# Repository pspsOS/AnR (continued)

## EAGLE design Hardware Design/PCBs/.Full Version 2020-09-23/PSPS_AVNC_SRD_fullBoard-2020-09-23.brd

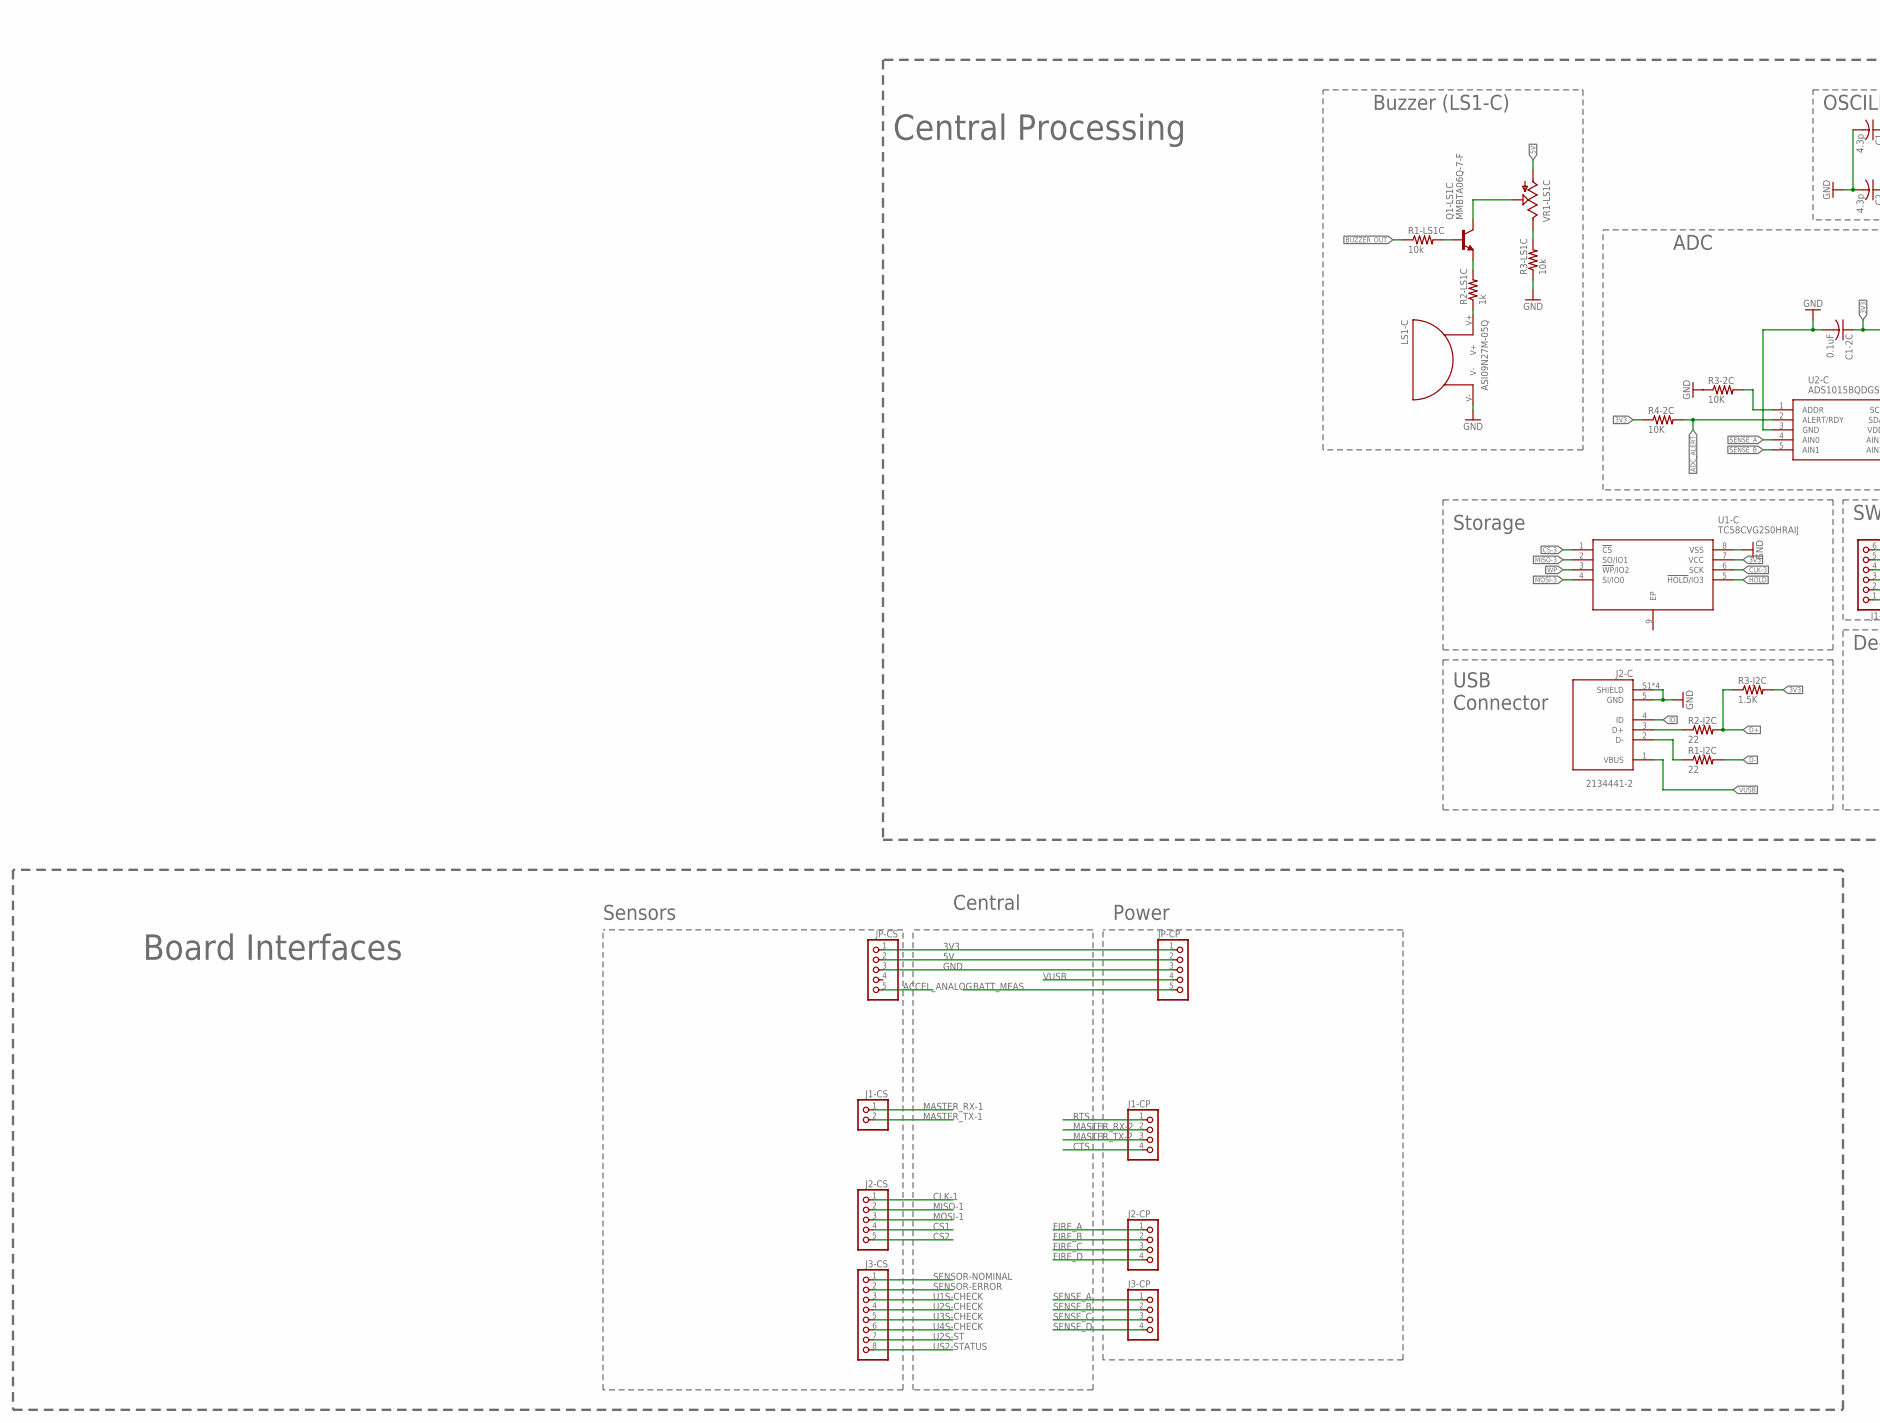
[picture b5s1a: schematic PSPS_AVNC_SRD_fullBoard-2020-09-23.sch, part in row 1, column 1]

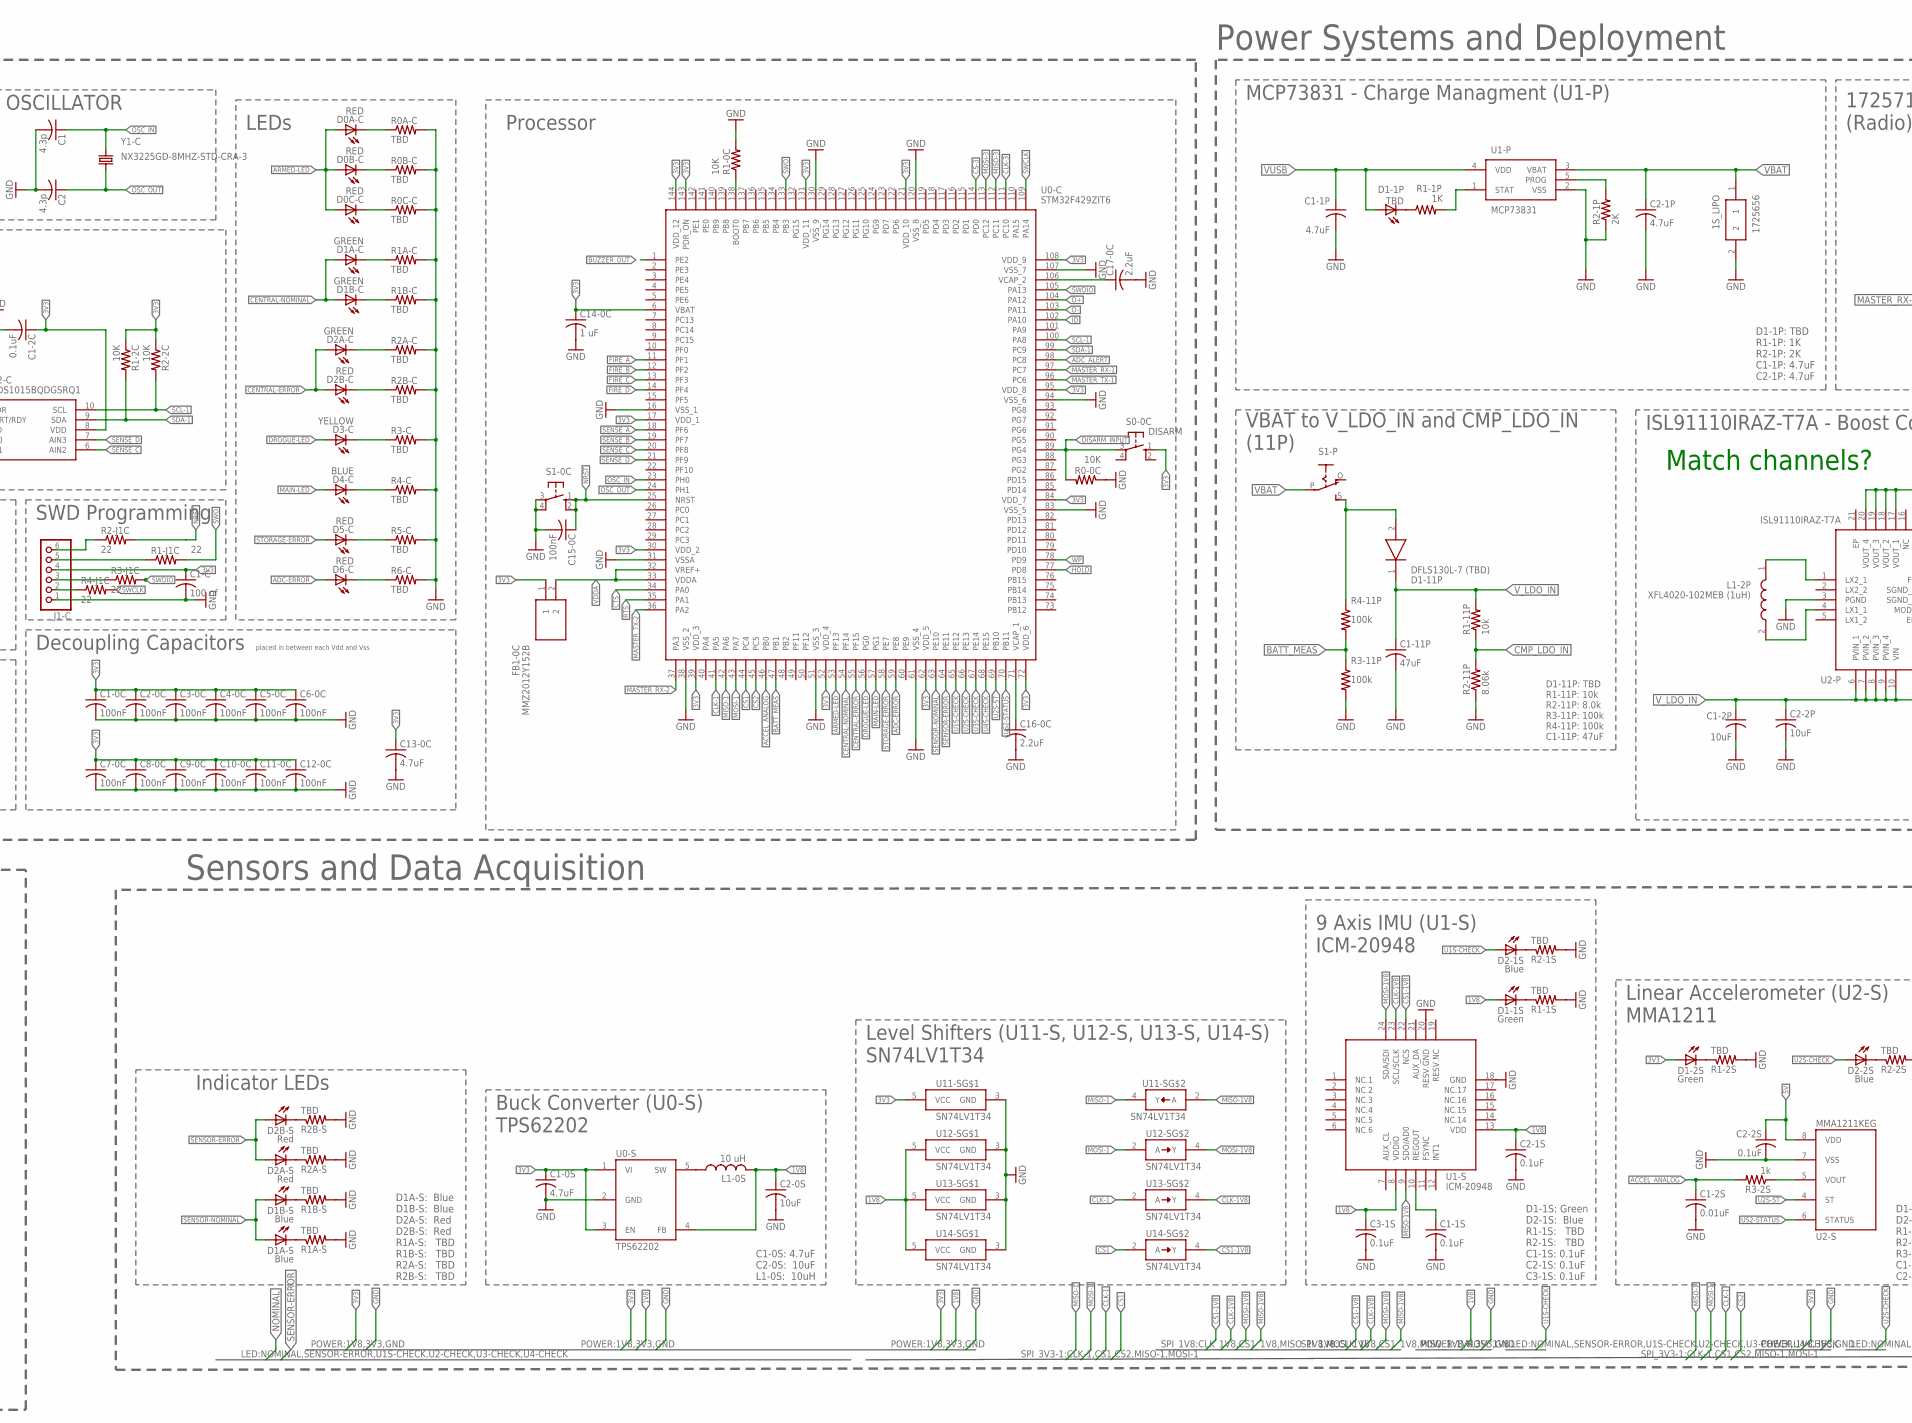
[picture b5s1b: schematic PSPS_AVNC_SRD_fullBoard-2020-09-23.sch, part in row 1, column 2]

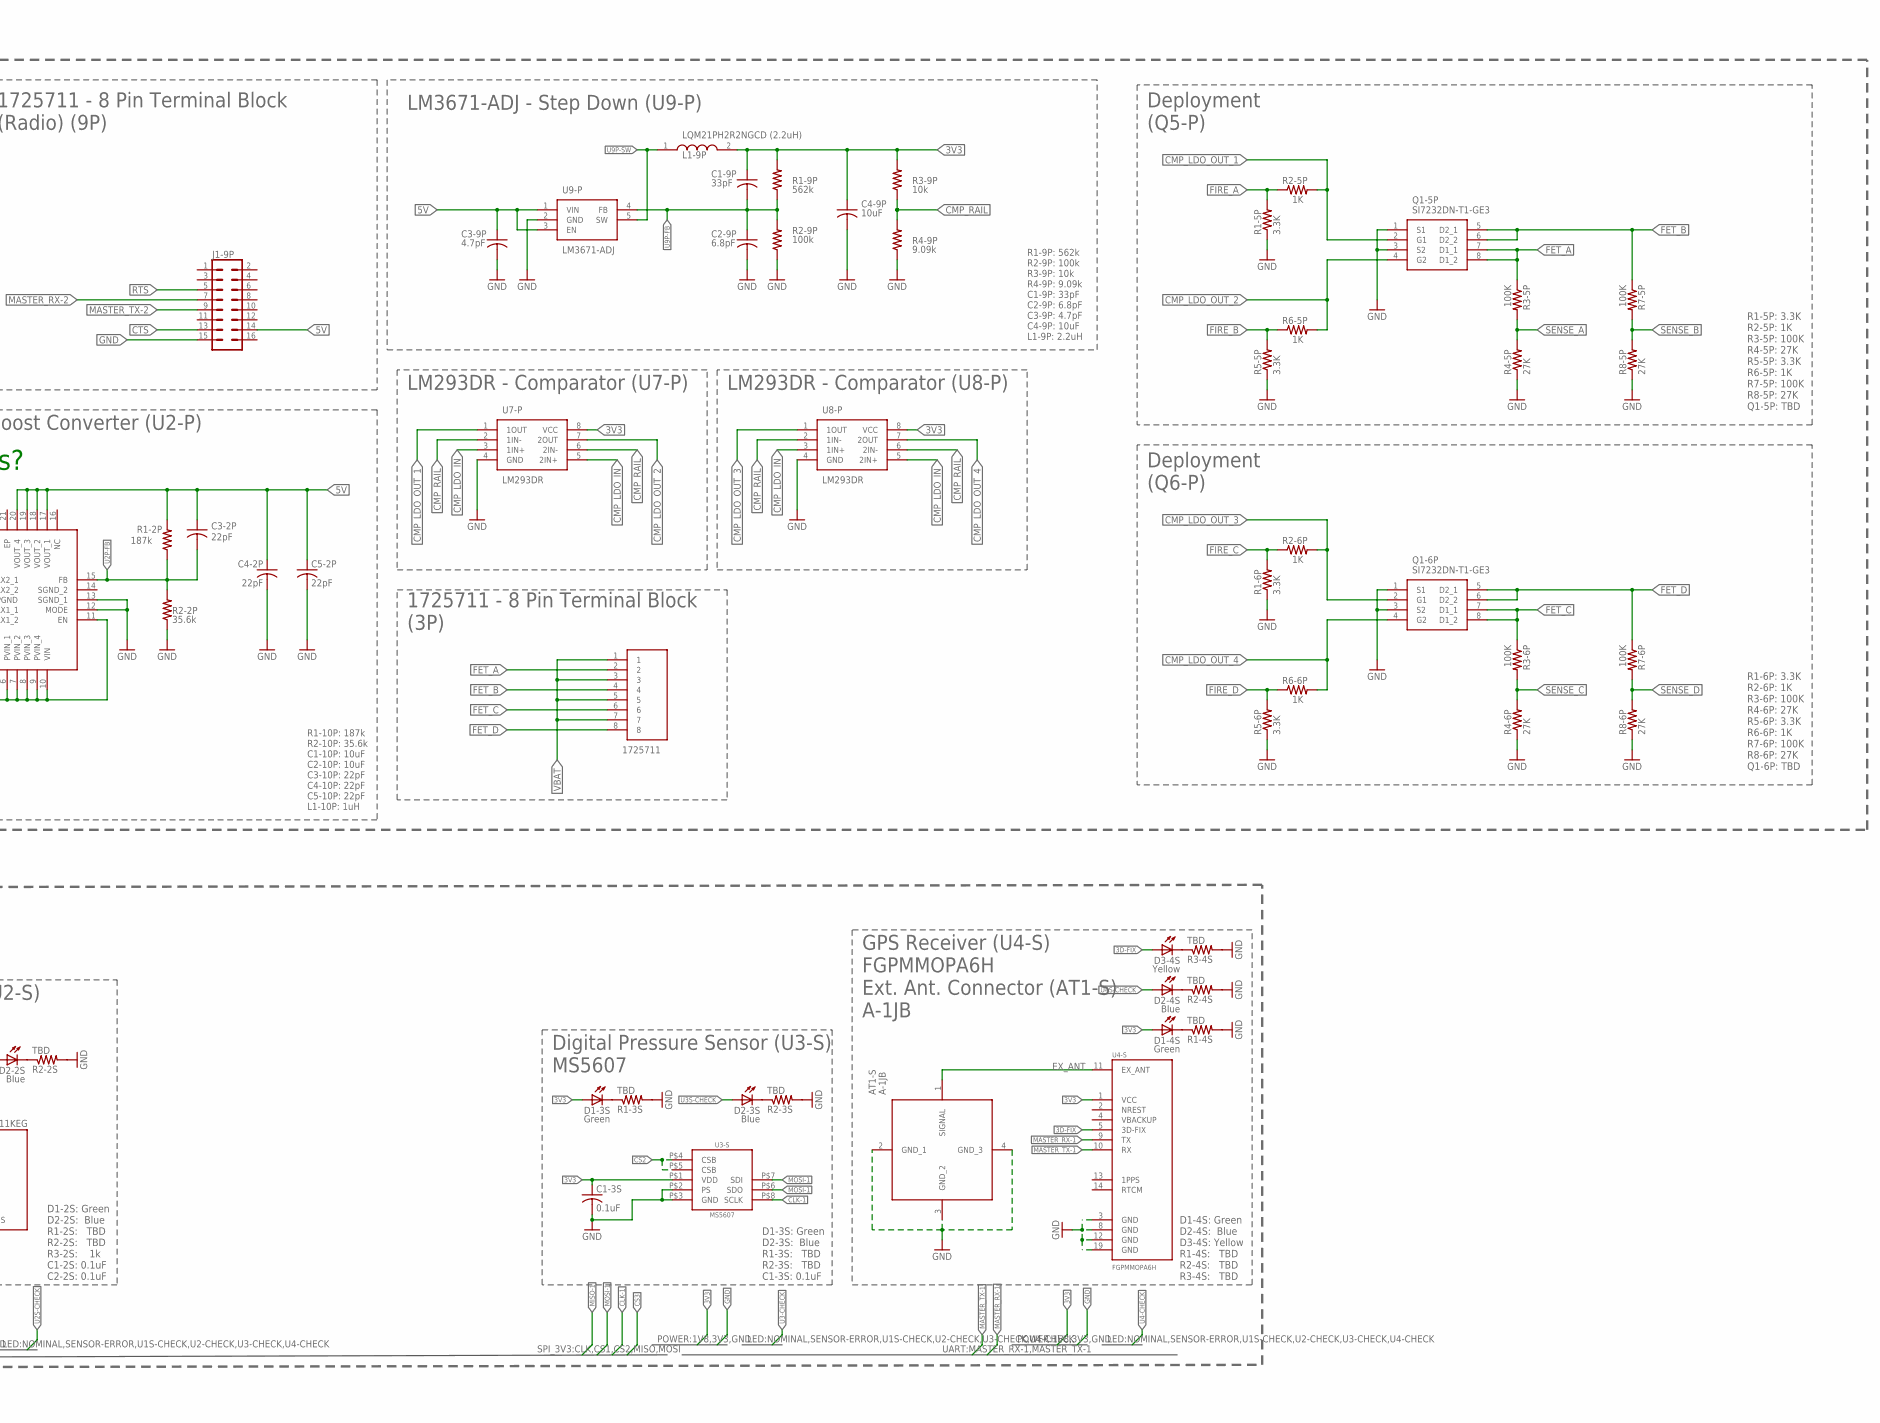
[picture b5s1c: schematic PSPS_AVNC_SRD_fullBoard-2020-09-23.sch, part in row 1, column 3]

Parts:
1S_LIPO: 1725656
AT1-S: A-1JB; A1JB
C1, C2: 4.3p; C0805
C1-0C, C2-0C, C3-0C, C4-0C, C5-0C, C6-0C, C7-0C, C8-0C, C9-0C, C10-0C, C11-0C, C12-0C, C15-0C: 100nF; C0805
C1-0S, C1-1P, C2-1P, C13-0C: 4.7uF; C0805
C1-1S, C1-2C, C1-3S, C2-1S, C2-2S, C3-1S: 0.1uF; C0805
C1-2P, C2-0S, C2-2P, C4-9P: 10uF; C0805
C1-2S: 0.01uF; C0805
C1-9P: 33pF; C0805
C1-11P: 47uF; C0805
C1-C: 100 nf; C0805
C2-9P: 6.8pF; C0805
C3-2P, C4-2P, C5-2P: 22pF; C0805
C3-9P: 4.7pF; C0805
C14-0C: 1 uF; C0805
C16-0C, C17-0C: 2.2uF; C0805
D0A-C, D0B-C, D0C-C, D2B-C, D5-C, D6-C: RED; CHIPLED_0805
D1-1P: TBD; CHIPLED_0805
D1-1S, D1-2S, D1-3S, D1-4S: Green; CHIPLED_0805
D1-11P: DFLS130L-7 (TBD); POWERDI_123
D1A-C, D1B-C, D2A-C: GREEN; CHIPLED_0805
D1A-S, D1B-S, D2-1S, D2-2S, D2-3S, D2-4S: Blue; CHIPLED_0805
D2A-S, D2B-S: Red; CHIPLED_0805
D3-4S: Yellow; CHIPLED_0805
D3-C: YELLOW; CHIPLED_0805
D4-C: BLUE; CHIPLED_0805
FB1-0C: MMZ2012Y152B; BEADC2012X105N
J1-9P: CONN_08X2; 2X8
J1-C: PINHD-1X6; 1X06
J1-CP, J2-CP, J3-CP: PINHD-1X4; 1X04
J1-CS: PINHD-1X2; 1X02
J2-C: 2134441-2; TE_2134441-2
J2-CS: PINHD-1X5; 1X05
J2-P: 1725711
J3-CS: PINHD-1X8; 1X08
JP-CP: PINHD-1X5; 1X05
JP-CS: PINHD-1X5; 1X05
L1-0S: 10 uH; PF0560NL
L1-2P: XFL4020-102MEB (1uH); XFL4020
L1-9P: LQM21PH2R2NGCD (2.2uH); INDC2012X100N
LS1-C: ASI09N27M-05Q
Q1-5P, Q1-6P: SI7232DN-T1-GE3; POWERPAK-1212-8
Q1-LS1C: MMBTA06Q-7-F; SOT23
R0-0C, R1-0C, R1-2C, R2-2C, R3-2C, R4-2C: 10K; R0805
R0A-C, R0B-C, R0C-C, R1A-C, R1B-C, R2A-C, R2B-C, R3-C, R4-C, R5-C, R6-C: TBD; M0805
R1-1P: 1K; R0805
R1-1S, R1-2S, R1-3S, R1-4S, R1A-S, R1B-S, R2-1S, R2-2S, R2-3S, R2-4S, R2A-S, R2B-S, R3-4S: TBD; R0805
R1-2P: 187k; R0805
R1-5P, R1-6P, R5-5P, R5-6P: 3.3K; M0805
R1-9P: 562k; R0805
R1-11P, R1-LS1C, R3-9P, R3-LS1C: 10k; R0805
R1-J1C, R1-J2C, R2-J1C, R2-J2C, R3-J1C, R4-J1C: 22; M0805
R2-1P: 2K; R0805
R2-2P: 35.6k; R0805
R2-5P, R2-6P, R6-5P, R6-6P: 1K; M0805
R2-9P, R3-11P, R4-11P: 100k; R0805
R2-11P: 8.06k; R0805
R2-LS1C, R3-2S: 1k; R0805
R3-5P, R3-6P, R7-5P, R7-6P: 100K; M0805
R3-J2C: 1.5K; M0805
R4-5P, R4-6P, R8-5P, R8-6P: 27K; M0805
R4-9P: 9.09k; R0805
S0-0C: DISARM; B3F-10XX
S1-0C: 10-XX; B3F-10XX
S1-P: EG1218S; EG1218
U0-C: STM32F429ZIT6; QFP50P2200X2200X160-144N
U0-S: TPS62202; SOT95P280X145-5
U1-C: TC58CVG2S0HRAIJ; SON127P800X600X80-9N
U1-P: MCP73831; SOT95P270X145-5N
U1-S: ICM-20948; QFN40P300X300X105-25T159X175
U2-C: ADS1015BQDGSRQ1; SOP50P490X110-10N
U2-P: ISL91110IRAZ-T7A; QFN50P400X400X100-21N
U2-S: MMA1211KEG; SOIC127P1041X355-16N
U3-S: MS5607
U4-S: FGPMMOPA6H; SOIC127P1800X470-20N
U7-P, U8-P: LM293DR; SOIC127P600X175-8N
U9-P: LM3671-ADJ; SOT95P280X145-5N
U11-S, U12-S, U13-S, U14-S: SN74LV1T34; SOT65P210X110-5
VR1-LS1C: TRIM_US-LI10; LI10
Y1-C: NX3225GD-8MHZ-STD-CRA-3; 3.2X2.5_KX-7

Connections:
1V8: C2-0S.1, C2-1S.1, C3-1S.1, D1-1S.A, L1-0S.P$2 (2), U0-S.4 (FB), U1-S.8 (VDDIO), U1-S.13 (VDD), U12-S.5 (VCC), U13-S.5 (VCC), U14-S.5 (VCC)
3D-FIX: D3-4S.A, U4-S.5 (3D-FIX)
3V3: C1-0C.1, C1-0S.1, C1-2C.1, C1-3S.1, C1-9P.1, C1-C.1, C2-0C.1, C3-0C.1, C4-0C.1, C4-9P.1, C5-0C.1, C6-0C.1, C7-0C.1, C8-0C.1, C9-0C.1, C10-0C.1, C11-0C.1, C12-0C.1, C13-0C.1, C14-0C.1, D1-2S.A, D1-3S.A, D1-4S.A, FB1-0C.1, J1-C.4, JP-CP.1, JP-CS.1, L1-9P.2, R1-2C.1, R1-9P.2, R2-2C.1, R3-9P.2, R3-J2C.2, R4-2C.1, S0-0C.1 (S), U0-C.6 (VBAT), U0-C.17 (VDD_1), U0-C.30 (VDD_2), U0-C.39 (VDD_3), U0-C.52 (VDD_4), U0-C.62 (VDD_5), U0-C.72 (VDD_6), U0-C.84 (VDD_7), U0-C.95 (VDD_8), U0-C.108 (VDD_9), U0-C.121 (VDD_10), U0-C.131 (VDD_11), U0-C.143 (PDR_ON), U0-C.144 (VDD_12), U0-S.1 (VI), U0-S.3 (EN), U1-C.7 (VCC), U2-C.8 (VDD), U3-S.P$1 (VDD), U4-S.1 (VCC), U7-P.8 (VCC), U8-P.8 (VCC), U11-S.5 (VCC)
5V: C2-2S.1, C3-2P.1, C3-9P.1, C4-2P.1, C5-2P.1, J1-9P.14, JP-CP.2, JP-CS.2, R1-2P.2, U2-P.17 (VOUT_1), U2-P.18 (VOUT_2), U2-P.19 (VOUT_3), U2-P.20 (VOUT_4), U2-S.8 (VDD), U9-P.1 (VIN), U9-P.3 (EN), VR1-LS1C.A
ACCEL_ANALOG: C1-2S.1, JP-CS.5, R3-2S.2, U0-C.46 (PB0)
ADC-ERROR: D6-C.A, U0-C.59 (PE8)
ADC_ALERT: R4-2C.2, U0-C.98 (PC8), U2-C.2 (ALERT/RDY)
ADDR: R3-2C.2, U2-C.1 (ADDR)
ARMED-LED: D0A-C.A, D0B-C.A, D0C-C.A, U0-C.53 (PF13)
BATT_MEAS: JP-CP.5, R3-11P.1, R4-11P.2, U0-C.47 (PB1)
BOOT0: R1-0C.1, U0-C.138 (BOOT0)
BUZZER_OUT: R1-LS1C.1, U0-C.1 (PE2)
CENTRAL-ERROR: D2A-C.A, D2B-C.A, U0-C.55 (PF15)
CENTRAL-NOMINAL: D1A-C.A, D1B-C.A, U0-C.54 (PF14)
CLK-1: J2-CS.1, U0-C.41 (PA5), U3-S.P$8 (SCLK), U13-S.2 (A)
CLK-1V8: U1-S.23 (SCL/SCLK), U13-S.4 (Y)
CLK-3: U0-C.111 (PC10), U1-C.6 (SCK)
CMP_LDO_IN: R1-11P.1, R2-11P.2, U7-P.3 (1IN+), U7-P.5 (2IN+), U8-P.3 (1IN+), U8-P.5 (2IN+)
CMP_LDO_OUT_1: Q1-5P.2 (G1), R2-5P.2, U7-P.1 (1OUT)
CMP_LDO_OUT_2: Q1-5P.4 (G2), R6-5P.2, U7-P.7 (2OUT)
CMP_LDO_OUT_3: Q1-6P.2 (G1), R2-6P.2, U8-P.1 (1OUT)
CMP_LDO_OUT_4: Q1-6P.4 (G2), R6-6P.2, U8-P.7 (2OUT)
CMP_RAIL: R3-9P.1, R4-9P.2, U7-P.2 (1IN-), U7-P.6 (2IN-), U8-P.2 (1IN-), U8-P.6 (2IN-)
CS1: J2-CS.4, U0-C.44 (PC4), U14-S.2 (A)
CS1-1V8: U1-S.22 (NCS), U14-S.4 (Y)
CS2: J2-CS.5, U0-C.45 (PC5), U3-S.P$4 (CSB), U3-S.P$5 (CSB)
CS-3: U0-C.114 (PD0), U1-C.1 (!CS)
CTS: J1-9P.13, J1-CP.4, U0-C.34 (PA0)
D0A-C_R0A-C: D0A-C.C, R0A-C.1
D0B-C_R0B-C: D0B-C.C, R0B-C.1
D0C-C_R0C-C: D0C-C.C, R0C-C.1
D1-1P_R1-1P: D1-1P.C, R1-1P.1
D1-1S_R1-1S: D1-1S.C, R1-1S.1
D1-2S_R1-2S: D1-2S.C, R1-2S.1
D1-3S_R1-3S: D1-3S.C, R1-3S.1
D1-4S_R1-4S: D1-4S.C, R1-4S.1
D1A-C_R1A-C: D1A-C.C, R1A-C.1
D1A-S_R1A-S: D1A-S.C, R1A-S.1
D1B-C_R1B-C: D1B-C.C, R1B-C.1
D1B-S_R1B-S: D1B-S.C, R1B-S.1
D2-1S_R2-1S: D2-1S.C, R2-1S.1
D2-2S_R2-2S: D2-2S.C, R2-2S.1
D2-3S_R2-3S: D2-3S.C, R2-3S.1
D2-4S_R2-4S: D2-4S.C, R2-4S.1
D2A-C_R2A-C: D2A-C.C, R2A-C.1
D2A-S_R2A-S: D2A-S.C, R2A-S.1
D2B-C_R2B-C: D2B-C.C, R2B-C.1
D2B-S_R2B-S: D2B-S.C, R2B-S.1
D3-4S_R3-4S: D3-4S.C, R3-4S.1
D3-C_R3-C: D3-C.C, R3-C.1
D4-C_R4-C: D4-C.C, R4-C.1
D5-C_R5-C: D5-C.C, R5-C.1
D6-C_R6-C: D6-C.C, R6-C.1
D+: R2-J2C.2, R3-J2C.1, U0-C.104 (PA12)
D+_R2-J1C: J2-C.3 (D+), R2-J2C.1
D-: R1-J2C.2, U0-C.103 (PA11)
D-_R1-J1C: J2-C.2 (D-), R1-J2C.1
DISARM_INPUT: R0-0C.2, S0-0C.3, U0-C.89 (PG4)
DROGUE-LED: D3-C.A, U0-C.56 (PG0)
EX_ANT: AT1-S.1 (SIGNAL), U4-S.11 (EX_ANT)
FET_A: J2-P.2, Q1-5P.7 (D1_1), Q1-5P.8 (D1_2), R3-5P.1
FET_B: J2-P.4, Q1-5P.5 (D2_1), Q1-5P.6 (D2_2), R7-5P.1
FET_C: J2-P.6, Q1-6P.7 (D1_1), Q1-6P.8 (D1_2), R3-6P.1
FET_D: J2-P.8, Q1-6P.5 (D2_1), Q1-6P.6 (D2_2), R7-6P.1
FIRE_A: J2-CP.1, R1-5P.2, R2-5P.1, U0-C.11 (PF1)
FIRE_B: J2-CP.2, R5-5P.2, R6-5P.1, U0-C.12 (PF2)
FIRE_C: J2-CP.3, R1-6P.2, R2-6P.1, U0-C.13 (PF3)
FIRE_D: J2-CP.4, R5-6P.2, R6-6P.1, U0-C.14 (PF4)
GND: 1S_LIPO.2, AT1-S.2 (GND_1), AT1-S.3 (GND_2), AT1-S.4 (GND_3), C1.2, C1-0C.2, C1-0S.2, C1-1P.2, C1-1S.2, C1-2C.2, C1-2P.2, C1-2S.2, C1-3S.2, C1-11P.2, C1-C.2, C2.2, C2-0C.2, C2-0S.2, C2-1P.2, C2-1S.2, C2-2P.2, C2-2S.2, C2-9P.2, C3-0C.2, C3-1S.2, C3-9P.2, C4-0C.2, C4-2P.2, C4-9P.2, C5-0C.2, C5-2P.2, C6-0C.2, C7-0C.2, C8-0C.2, C9-0C.2, C10-0C.2, C11-0C.2, C12-0C.2, C13-0C.2, C14-0C.2, C15-0C.2, C16-0C.2, C17-0C.2, J1-9P.15, J1-C.1, J2-C.5 (GND), J2-C.S1 (SHIELD), J2-C.S2 (SHIELD), J2-C.S3 (SHIELD), J2-C.S4 (SHIELD), JP-CP.3, JP-CS.3, LS1-C.V-, Q1-5P.1 (S1), Q1-5P.3 (S2), Q1-6P.1 (S1), Q1-6P.3 (S2), R0-0C.1, R0A-C.2, R0B-C.2, R0C-C.2, R1-0C.2, R1-1S.2, R1-2S.2, R1-3S.2, R1-4S.2, R1-5P.1, R1-6P.1, R1A-C.2, R1A-S.2, R1B-C.2, R1B-S.2, R2-1P.1, R2-1S.2, R2-2P.1, R2-2S.2, R2-3S.2, R2-4S.2, R2-9P.1, R2-11P.1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
HOLD: U0-C.77 (PD8), U1-C.5 (!HOLD!/IO3)
ID: J2-C.4 (ID), U0-C.102 (PA10)
J1-C_R1-J1C: J1-C.5, R1-J1C.1
J1-C_R2-J1C: J1-C.6, R2-J1C.1
MAIN-LED: D4-C.A, U0-C.57 (PG1)
MASTER_RX-1: J1-CS.1, U0-C.97 (PC7), U4-S.9 (TX)
MASTER_RX-2: J1-9P.7, J1-CP.2, U0-C.37 (PA3)
MASTER_TX-1: J1-CS.2, U0-C.96 (PC6), U4-S.10 (RX)
MASTER_TX-2: J1-9P.9, J1-CP.3, U0-C.36 (PA2)
MISO-1: J2-CS.2, U0-C.42 (PA6), U11-S.4 (Y)
MISO-1V8: U1-S.9 (SDO/AD0), U11-S.2 (A)
MISO-3: U0-C.112 (PC11), U1-C.2 (SO/IO1)
MOSI-1: J2-CS.3, U0-C.43 (PA7), U3-S.P$6 (SDO), U3-S.P$7 (SDI), U12-S.2 (A)
MOSI-1V8: U1-S.24 (SDA/SDI), U12-S.4 (Y)
MOSI-3: U0-C.113 (PC12), U1-C.4 (SI/IO0)
NRST: C15-0C.1, R2-J1C.2, S1-0C.1 (S), S1-0C.2 (S1), U0-C.25 (NRST)
OSC_IN: C1.1, U0-C.23 (PH0), Y1-C.3 (2)
OSC_OUT: C2.1, U0-C.24 (PH1), Y1-C.1
Q1-LS1C_R2-LS1C: Q1-LS1C.3 (E), R2-LS1C.2
R1-LS1C_Q1-LS1C: Q1-LS1C.1 (B), R1-LS1C.2
R2-LS1C_LS1-C: LS1-C.V+, R2-LS1C.1
REGOUT: C1-1S.1, U1-S.10 (REGOUT)
RTS: J1-9P.5, J1-CP.1, U0-C.35 (PA1)
SCL-1: R2-2C.2, U0-C.100 (PA8), U2-C.10 (SCL)
SDA-1: R1-2C.2, U0-C.99 (PC9), U2-C.9 (SDA)
SENSE_A: J3-CP.1, R3-5P.2, R4-5P.2, U0-C.18 (PF6), U2-C.4 (AIN0)
SENSE_B: J3-CP.2, R7-5P.2, R8-5P.2, U0-C.19 (PF7), U2-C.5 (AIN1)
SENSE_C: J3-CP.3, R3-6P.2, R4-6P.2, U0-C.20 (PF8), U2-C.6 (AIN2)
SENSE_D: J3-CP.4, R7-6P.2, R8-6P.2, U0-C.21 (PF9), U2-C.7 (AIN3)
SENSOR-ERROR: D2A-S.A, D2B-S.A, J3-CS.2, U0-C.64 (PE11)
SENSOR-NOMINAL: D1A-S.A, D1B-S.A, J3-CS.1, U0-C.63 (PE10)
STORAGE-ERROR: D5-C.A, U0-C.58 (PE7)
SWCLK: J1-C.2, R4-J1C.1, R4-J1C.2, U0-C.109 (PA14)
SWDIO: J1-C.3, R3-J1C.1, R3-J1C.2, U0-C.105 (PA13)
SWO: R1-J1C.2, U0-C.133 (PB3)
U0S-SW: L1-0S.P$1 (1), U0-S.5 (SW)
U1P-PROG: R2-1P.2, U1-P.5 (PROG)
U1P-STAT: R1-1P.2, U1-P.1 (STAT)
U1S-CHECK: D2-1S.A, J3-CS.3, U0-C.65 (PE12)
U2P-FB: C3-2P.2, R1-2P.1, R2-2P.2, U2-P.15 (FB)
U2S-CHECK: D2-2S.A, J3-CS.4, U0-C.66 (PE13)
U2S-ST: J3-CS.7, U0-C.69 (PB10), U2-S.4 (ST)
U3S-CHECK: D2-3S.A, J3-CS.5, U0-C.67 (PE14)
U4S-CHECK: D2-4S.A, J3-CS.6, U0-C.68 (PE15)
U9P-FB: C1-9P.2, C2-9P.1, R1-9P.1, R2-9P.2, U9-P.4 (FB)
U9P-LX1_1: L1-2P.2, U2-P.4 (LX1_1)
U9P-LX2_1: L1-2P.1, U2-P.1 (LX2_1)
U9P-SW: L1-9P.1, U9-P.5 (SW)
US2-STATUS: J3-CS.8, U0-C.70 (PB11), U2-S.6 (STATUS)
VBAT: 1S_LIPO.1, C2-1P.1, J2-P.1, J2-P.3, J2-P.5, J2-P.7, S1-P.P, U1-P.3 (VBAT)
VBAT_AFTER_SWITCH: D1-11P.2 (A), R4-11P.1, S1-P.S
VCAP_1: C16-0C.1, U0-C.71 (VCAP_1)
VCAP_2: C17-0C.1, U0-C.106 (VCAP_2)
VDDA: FB1-0C.2, U0-C.32 (VREF+), U0-C.33 (VDDA)
VOUT: R3-2S.1, U2-S.5 (VOUT)
VR1-LS1C: Q1-LS1C.2 (C), VR1-LS1C.S
VR1-LS1C_R3-LS1C: R3-LS1C.2, VR1-LS1C.E
VUSB: C1-1P.1, D1-1P.A, J2-C.1 (VBUS), JP-CP.4, U1-P.4 (VDD)
V_LDO_IN: C1-2P.1, C1-11P.1, C2-2P.1, D1-11P.1 (K), R1-11P.2, U2-P.6 (PVIN_1), U2-P.7 (PVIN_2), U2-P.8 (PVIN_3), U2-P.9 (PVIN_4), U2-P.10 (VIN), U2-P.11 (EN)
WP: U0-C.78 (PD9), U1-C.3 (!WP!/IO2)

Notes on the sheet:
Level Shifters (U11-S, U12-S, U13-S, U14-S) SN74LV1T34
9 Axis IMU (U1-S) ICM-20948
Buck Converter (U0-S) TPS62202
C1-0S: 4.7uF C2-0S: 10uF L1-0S: 10uH
D1-1S: Green D2-1S: Blue R1-1S: TBD R2-1S: TBD C1-1S: 0.1uF C2-1S: 0.1uF C3-1S: 0.1uF
Linear Accelerometer (U2-S) MMA1211
D1-2S: Green D2-2S: Blue R1-2S: TBD R2-2S: TBD R3-2S: 1k C1-2S: 0.1uF C2-2S: 0.1uF
Digital Pressure Sensor (U3-S) MS5607
D1-3S: Green D2-3S: Blue R1-3S: TBD R2-3S: TBD C1-3S: 0.1uF
GPS Receiver (U4-S) FGPMMOPA6H Ext. Ant. Connector (AT1-S) A-1JB
D1-4S: Green D2-4S: Blue D3-4S: Yellow R1-4S: TBD R2-4S: TBD R3-4S: TBD
D1A-S: Blue D1B-S: Blue D2A-S: Red D2B-S: Red R1A-S: TBD R1B-S: TBD R2A-S: TBD R2B-S: TBD
Indicator LEDs
Sensors and Data Acquisition
Central Processing
Power Systems and Deployment
placed in between each Vdd and Vss
Deployment (Q5-P)
R1-5P: 3.3K R2-5P: 1K R3-5P: 100K R4-5P: 27K R5-5P: 3.3K R6-5P: 1K R7-5P: 100K R8-5P: 27K Q1-5P: TBD
Processor
Storage
Decoupling Capacitors
SWD Programming
LEDs
ADC
USB Connector
1725711 - 8 Pin Terminal Block (3P)
MCP73831 - Charge Managment (U1-P)
D1-1P: TBD R1-1P: 1K R2-1P: 2K C1-1P: 4.7uF C2-1P: 4.7uF
LM3671-ADJ - Step Down (U9-P)
R1-9P: 562k R2-9P: 100k R3-9P: 10k R4-9P: 9.09k C1-9P: 33pF C2-9P: 6.8pF C3-9P: 4.7pF C4-9P: 10uF L1-9P: 2.2uH
LM293DR - Comparator (U7-P)
ISL91110IRAZ-T7A - Boost Converter (U2-P)
R1-10P: 187k R2-10P: 35.6k C1-10P: 10uF C2-10P: 10uF C3-10P: 22pF C4-10P: 22pF C5-10P: 22pF L1-10P: 1uH
VBAT to V_LDO_IN and CMP_LDO_IN (11P)
D1-11P: TBD R1-11P: 10k R2-11P: 8.0k R3-11P: 100k R4-11P: 100k C1-11P: 47uF
Deployment (Q6-P)
R1-6P: 3.3K R2-6P: 1K R3-6P: 100K R4-6P: 27K R5-6P: 3.3K R6-6P: 1K R7-6P: 100K R8-6P: 27K Q1-6P: TBD
LM293DR - Comparator (U8-P)
1725711 - 8 Pin Terminal Block (Radio) (9P)

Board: 2 copper layers, 180 parts (4 on the bottom side), 129 nets, no tracks yet.

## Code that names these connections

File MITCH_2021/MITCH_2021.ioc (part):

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Mcu.Name=STM32F429ZITx
Mcu.Package=LQFP144
Mcu.UserName=STM32F429ZITx
PA1.Mode=CTS_RTS
PA1.Signal=USART2_RTS
PA10.Mode=OTG/Dual_Role_Device
PA10.Signal=USB_OTG_FS_ID
PA11.Mode=OTG/Dual_Role_Device
PA11.Signal=USB_OTG_FS_DM
PA12.Mode=OTG/Dual_Role_Device
PA12.Signal=USB_OTG_FS_DP
PA13.Signal=SYS_JTMS-SWDIO
PA14.Signal=SYS_JTCK-SWCLK
PA2.Mode=Asynchronous
PA2.Signal=USART2_TX
PA3.Mode=Asynchronous
PA3.Signal=USART2_RX
PA5.Mode=Full_Duplex_Master
PA5.Signal=SPI1_SCK
PA6.Mode=Full_Duplex_Master
PA6.Signal=SPI1_MISO
PA7.Mode=Full_Duplex_Master
PA7.Signal=SPI1_MOSI
PA8.Mode=I2C
PA8.Signal=I2C3_SCL
PB0.GPIOParameters=GPIO_Label
PB0.GPIO_Label=ACCEL_ANALOG
PB0.Signal=SharedAnalog_PB0
PB1.GPIOParameters=GPIO_Label
PB1.GPIO_Label=BATT_MEAS
PB1.Signal=SharedAnalog_PB1
PB10.GPIOParameters=GPIO_Label
PB10.GPIO_Label=US2-ST
PB10.Signal=GPIO_Output
PB11.GPIOParameters=GPIO_Label
PB11.GPIO_Label=US2-STATUS
PB11.Signal=GPIO_Input
PB12.GPIOParameters=GPIO_Label
PB12.GPIO_Label=CHECK_HARDWARE_DEPLOYMENT_DISABLE
PB12.Signal=GPIO_Input
PB13.Signal=GPIO_Output
PB14.Signal=GPIO_Output
PB15.Signal=GPIO_Output
PB3.Signal=SYS_JTDO-SWO
PC10.Mode=Full_Duplex_Master
PC10.Signal=SPI3_SCK
PC11.Mode=Full_Duplex_Master
PC11.Signal=SPI3_MISO
PC12.Mode=Full_Duplex_Master
PC12.Signal=SPI3_MOSI
PC4.GPIOParameters=GPIO_Label
PC4.GPIO_Label=CS1
PC4.Signal=GPIO_Output
PC5.GPIOParameters=GPIO_Label
PC5.GPIO_Label=CS2
PC5.Signal=GPIO_Output
PC6.Mode=Asynchronous
PC6.Signal=USART6_TX
PC7.Mode=Asynchronous
PC7.Signal=USART6_RX
PC8.GPIOParameters=GPIO_Label
PC8.GPIO_Label=ADC_ALERT
PC8.Signal=GPIO_Input
PC9.Mode=I2C
PC9.Signal=I2C3_SDA
PD0.GPIOParameters=GPIO_Label
PD0.GPIO_Label=CS3
PD0.Signal=GPIO_Output
PD1.GPIOParameters=GPIO_Label
PD1.GPIO_Label=WP
PD1.Signal=GPIO_Output
PD10.Signal=GPIO_Output
PD11.Signal=GPIO_Output
PD12.Signal=GPIO_Output
PD13.Signal=GPIO_Output
PD2.GPIOParameters=GPIO_Label
PD2.GPIO_Label=HOLD
PD2.Signal=GPIO_Output
PD3.Mode=CTS_RTS
PD3.Signal=USART2_CTS
PD8.Signal=GPIO_Output
PD9.Signal=GPIO_Output
PE10.GPIOParameters=GPIO_Label
PE10.GPIO_Label=SENSOR-NOMINAL
PE10.Signal=GPIO_Output
PE11.GPIOParameters=GPIO_Label
PE11.GPIO_Label=SENSOR-ERROR
PE11.Signal=GPIO_Output
PE12.GPIOParameters=GPIO_Label
PE12.GPIO_Label=U1S-CHECK
PE12.Signal=GPIO_Output
PE13.GPIOParameters=GPIO_Label
PE13.GPIO_Label=U2S-CHECK
PE13.Signal=GPIO_Output
PE14.GPIOParameters=GPIO_Label
PE14.GPIO_Label=U3S-CHECK
PE14.Signal=GPIO_Output
PE15.GPIOParameters=GPIO_Label
PE15.GPIO_Label=U4S-CHECK
PE15.Signal=GPIO_Output
PE2.GPIOParameters=GPIO_Label
PE2.GPIO_Label=BUZZER_OUT
PE2.Signal=GPIO_Output
PE7.GPIOParameters=GPIO_Label
PE7.GPIO_Label=STORAGE-ERROR
PE7.Signal=GPIO_Output
PE8.GPIOParameters=GPIO_Label
PE8.GPIO_Label=ADC-ERROR
PE8.Signal=GPIO_Output
PF1.GPIOParameters=GPIO_Label
PF1.GPIO_Label=FIRE_A
PF1.Signal=GPIO_Output
PF13.GPIOParameters=GPIO_Label
PF13.GPIO_Label=ARMED_LED
PF13.Signal=GPIO_Output
PF14.GPIOParameters=GPIO_Label
PF14.GPIO_Label=CENTRAL-NOMINAL
PF14.Signal=GPIO_Output
PF15.GPIOParameters=GPIO_Label
PF15.GPIO_Label=CENTRAL-ERROR
PF15.Signal=GPIO_Output
PF2.GPIOParameters=GPIO_Label
PF2.GPIO_Label=FIRE_B
PF2.Signal=GPIO_Output
PF3.GPIOParameters=GPIO_Label
PF3.GPIO_Label=FIRE_C
PF3.Signal=GPIO_Output
PF4.GPIOParameters=GPIO_Label
PF4.GPIO_Label=FIRE_D
PF4.Signal=GPIO_Output
PF6.GPIOParameters=GPIO_Label
PF6.GPIO_Label=SENSE_A
PF6.Signal=GPIO_Input
PF7.GPIOParameters=GPIO_Label
PF7.GPIO_Label=SENSE_B
PF7.Signal=GPIO_Input
PF8.GPIOParameters=GPIO_Label
PF8.GPIO_Label=SENSE_C
PF8.Signal=GPIO_Input
PF9.GPIOParameters=GPIO_Label
PF9.GPIO_Label=SENSE_D
PF9.Signal=GPIO_Input
PG0.GPIOParameters=GPIO_Label
PG0.GPIO_Label=DROGUE-LED
PG0.Signal=GPIO_Output
PG1.GPIOParameters=GPIO_Label
PG1.GPIO_Label=MAIN-LED
PG1.Signal=GPIO_Output
PG4.GPIOParameters=GPIO_Label
PG4.GPIO_Label=DISARM_INPUT
PG4.Signal=GPIO_Input
PH0/OSC_IN.Mode=HSE-External-Oscillator
PH0/OSC_IN.Signal=RCC_OSC_IN
PH1/OSC_OUT.Mode=HSE-External-Oscillator
PH1/OSC_OUT.Signal=RCC_OSC_OUT
RCC.HSE_VALUE=8000000
RCC.SYSCLKFreq_VALUE=16000000
board=custom

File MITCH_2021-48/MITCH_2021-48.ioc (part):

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Mcu.Name=STM32F411C(C-E)Ux
Mcu.Package=UFQFPN48
Mcu.UserName=STM32F411CEUx
PA0-WKUP.Mode=CTS_RTS
PA0-WKUP.Signal=USART2_CTS
PA1.Mode=CTS_RTS
PA1.Signal=USART2_RTS
PA10.Mode=Asynchronous
PA10.Signal=USART1_RX
PA11.GPIOParameters=GPIO_Label
PA11.GPIO_Label=BUZZER_OUT
PA11.Signal=GPIO_Output
PA12.GPIOParameters=GPIO_Label
PA12.GPIO_Label=BUTTON_IN
PA12.Signal=GPIO_Input
PA13.Mode=Serial_Wire
PA13.Signal=SYS_JTMS-SWDIO
PA14.Mode=Serial_Wire
PA14.Signal=SYS_JTCK-SWCLK
PA15.GPIOParameters=GPIO_Label
PA15.GPIO_Label=HDD_CHECK
PA15.Signal=GPIO_Input
PA2.Mode=Asynchronous
PA2.Signal=USART2_TX
PA3.Mode=Asynchronous
PA3.Signal=USART2_RX
PA4.GPIOParameters=GPIO_Label
PA4.GPIO_Label=ARMING_MEAS
PA4.Signal=ADCx_IN4
PA5.Mode=Full_Duplex_Master
PA5.Signal=SPI1_SCK
PA6.Mode=Full_Duplex_Master
PA6.Signal=SPI1_MISO
PA7.Mode=Full_Duplex_Master
PA7.Signal=SPI1_MOSI
PA8.GPIOParameters=GPIO_Label
PA8.GPIO_Label=SPI2_LE
PA8.Signal=GPIO_Output
PA9.Mode=Asynchronous
PA9.Signal=USART1_TX
PB0.GPIOParameters=GPIO_Label
PB0.GPIO_Label=BATT_MEAS
PB0.Signal=ADCx_IN8
PB1.GPIOParameters=GPIO_Label
PB1.GPIO_Label=ACCEL_ANALOG
PB1.Signal=ADCx_IN9
PB10.GPIOParameters=GPIO_Label
PB10.GPIO_Label=SPI1_REG
PB10.Signal=GPIO_Output
PB12.GPIOParameters=GPIO_Label
PB12.GPIO_Label=SPI2_REG
PB12.Signal=GPIO_Output
PB13.Mode=Full_Duplex_Master
PB13.Signal=SPI2_SCK
PB14.Mode=Full_Duplex_Master
PB14.Signal=SPI2_MISO
PB15.Mode=Full_Duplex_Master
PB15.Signal=SPI2_MOSI
PB2.GPIOParameters=GPIO_Label
PB2.GPIO_Label=SPI1_LE
PB2.Signal=GPIO_Output
PB3.Signal=SYS_JTDO-SWO
PB4.GPIOParameters=GPIO_Label
PB4.GPIO_Label=FIRE_A
PB4.Signal=GPIO_Output
PB5.GPIOParameters=GPIO_Label
PB5.GPIO_Label=FIRE_B
PB5.Signal=GPIO_Output
PB6.GPIOParameters=GPIO_Label
PB6.GPIO_Label=FIRE_C
PB6.Signal=GPIO_Output
PB7.GPIOParameters=GPIO_Label
PB7.GPIO_Label=FIRE_D
PB7.Signal=GPIO_Output
PB8.GPIOParameters=GPIO_Label
PB8.GPIO_Label=SENSE_D
PB8.Signal=GPIO_Output
PB9.GPIOParameters=GPIO_Label
PB9.GPIO_Label=SENSE_C
PB9.Signal=GPIO_Output
PC13-ANTI_TAMP.GPIOParameters=GPIO_Label
PC13-ANTI_TAMP.GPIO_Label=SENSE_B
PC13-ANTI_TAMP.Signal=GPIO_Input
PC14-OSC32_IN.GPIOParameters=GPIO_Label
PC14-OSC32_IN.GPIO_Label=SENSE_A
PC14-OSC32_IN.Signal=GPIO_Input
PC15-OSC32_OUT.GPIOParameters=GPIO_Label
PC15-OSC32_OUT.GPIO_Label=LD1
PC15-OSC32_OUT.Signal=GPIO_Output
PH0\ -\ OSC_IN.GPIOParameters=GPIO_Label
PH0\ -\ OSC_IN.GPIO_Label=LD2
PH0\ -\ OSC_IN.Signal=GPIO_Output
PH1\ -\ OSC_OUT.GPIOParameters=GPIO_Label
PH1\ -\ OSC_OUT.GPIO_Label=ARMING_EN
PH1\ -\ OSC_OUT.Signal=GPIO_Output
RCC.HSE_VALUE=25000000
RCC.SYSCLKFreq_VALUE=16000000
board=custom

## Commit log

2020-12-13 Generated Project Files
2020-12-13 Setup workplace
2020-12-13 Setup Libraries
    fixed mess
2020-12-13 Started over
    reduced to ashes
2020-12-13 Added library files
2020-12-13 anotha one
2020-12-13 Sending it back
2020-12-13 Corrected Spelling Mistake
    Montoring -> Monitoring
    Also generated:
    \AnR\MITCH_2021\Drivers\CMSIS\Device\ST\STM32F4xx\Source\Templates\system_stm32f4xx.c
    (We don't know what it does) ¯\_(ツ)_/¯
2020-12-15 Example Commit
2020-12-15 another example
2020-12-15 Added common.h
    header file to include info common to all tasks/ libraries
2020-12-16 Expanded common.h
    Added/Improved definitions for
    - daqStatusData
    - gpsData
    - bmpData
    - imuData
2020-12-17 Updated interface structs
2020-12-22 Created Common Source File & getTimeStamp()
    Created common.c
    Added template getTimeStamp() to common
2020-12-23 Started NMEA parsing
2020-12-23 Updated Functions
    fixed mess
2020-12-24 Created Transmission Prototype Functions
2020-12-24 Created Acquisition Prototype Functions
2020-12-24 Monitoring function prototypes
2020-12-24 controlLogic Function Prototypes
2020-12-24 Update .gitignore
    Pls work for once
2020-12-24 Storage function prototypes
    Added storage function prototypes
    Also included "common.h" to all the tasks but processing bc that still isn't figured out so I didn't want to touch it
2020-12-25 Created _findNmeaAddr for gps parsing
2020-12-25 Experimenting with doxygen support
2020-12-26 Created _splitNmea() function
2020-12-26 Eclipse Setup Test Cleanup
2020-12-26 Setup Project for sharing with eclipse
2020-12-26 Fixed ifndef command for exclusion
2020-12-28 Started GPS Parsing
2020-12-29 Shortened variable names
    Consolidated byte into uint8_t
    Shortened uint8_t to u8
    Shortened uint16_t to u16
    Shortened uint32_t to u32
2020-12-29 Start acquisition setup
2020-12-29 Processing function prototypes
2020-12-29 Vishnu broke it
2020-12-29 Fixed my mess
2020-12-29 Added Suffix to Processing
2020-12-29 Added Suffix to Acquisition
2020-12-29 Updated controlLogic function names
2020-12-29 Added Suffixes to Transmission Functions
2020-12-29 Added more acquisition interface structs
2020-12-29 Updated Documentation in Transmission
2020-12-29 Updated common.h with monitoringData
2020-12-29 added update and lock in monitoring
2020-12-29 Added semaphores to acquisition interface structs
2020-12-29 externed all acquisition interface structs
2020-12-29 Fixed Jeff's mess
2020-12-29 Made read example in getData_T
2020-12-29 updated monitoring.c
2020-12-29 Updated constants and asserts
    Included nominal mode flow constants, defined extern mode flow variables, added asserts and NDEBUG logic
2020-12-29 updated monitoring with ifndef
2020-12-29 added comments to monitoring.c
2020-12-29 Updated NDEBUG location
2020-12-29 Transmission and Common update
2020-12-29 Fixed Transmission.h
2020-12-29 updated monitoring and main.c function calls
2020-12-29 updated monitoring.h
2020-12-29 Updated global variables
2020-12-29 Created pointyEndUp_P()
2020-12-29 Updated code structure
2020-12-29 Fixed logic -- Stable build
2020-12-31 Created print() macro for debug only
    Also corrected documentation for _splitNmea
2020-12-31 Implemented debug sensor setup functions
2020-12-31 Added second print macro without parameters
2021-01-01 Implemented txt file sensor simulation
2021-01-01 Expanded Acquisition flow chart implementation
2021-01-01 Corrected compiler warnings
2021-01-01 Added assertFileNames debug setting
2021-01-02 Added notifyWhenReadAborted debug setting
2021-01-02 Encapsulated debug sensor setup
    Also created settings print function
2021-01-03 Started documentation in README files
    It's a Christmas Miracle!
2021-01-03 Implemented Monitoring debug simulation
2021-01-03 editied monitoring functions for debug
2021-01-04 Added hardware deployment check to monitoring
2021-01-04 Initial Code for Processing
2021-01-04 Cleaned up Monitoring.c
2021-01-04 Update common.h
    updated list pointers
2021-01-04 Updated Monitoring.h with _M
2021-01-04 Added list functions
2021-01-04 Bug fixed
2021-01-04 Fixed Vishnu's mess by commenting it out
2021-01-04 Updated monitoring.md
2021-01-06 Added DEFAULT_DAQ_SCALER constant to common
2021-01-06 Improved documentation for Acquisition
2021-01-06 Fixed typo in file names
2021-01-09 Fixed linked list creation and updated controlLogic outline
2021-01-09 Updated processing with some functions
2021-01-09 missing code
2021-01-09 Updated List Functions
2021-01-09 Commented out Processing errors
2021-01-09 Returned true from processing bool functions to remove warnings
2021-01-09 Updated Acquisition documentation
2021-01-09 Updated Project Settings
2021-01-09 Pushed my own local language.settings.xml file
2021-01-10 Trying to get stable build in CubeMX
    Error Message:
    C:/Users/Jeff/Documents/GitHub/AnR/MITCH_2021/Debug/../Src/sysmem.c:55: multiple definition of `_sbrk'
    Src/syscalls.o:C:/Users/Jeff/Documents/GitHub/AnR/MITCH_2021/Debug/../Src/syscalls.c:118: first defined here
    startup/startup_stm32f429zitx.o:(.isr_vector+0x0): multiple definition of `g_pfnVectors'
    startup/startup_stm32f429xx.o:(.isr_vector+0x0): first defined here
    startup/startup_stm32f429zitx.o: In function `DMA2D_IRQHandler':
2021-01-10 Update .gitnore to exclude builds
2021-01-10 Fixed warning of not returning bool from storageSetup
2021-01-10 Revert "Updated Project Settings"
    This reverts commit 26fb79c6fef0c98073ad5025317dcc7857182b26.
2021-01-10 Revert "Revert "Updated Project Settings""
    This reverts commit 479d4205e1e0c8f1c99ee10e338188257269b593.
2021-01-10 Made build stable in both Eclipse and STM32 IDE
2021-01-10 Uncommented NDEBUG
2021-01-10 Added ACCEL_ANALOG and BATT_MEAS to project files
2021-01-11 Continued setting up GPIO for adc
2021-01-11 Added Dawson's original source code
2021-01-11 Implemented bmpRead in hardware
2021-01-12 Tweaked GPIO settings
2021-01-14 Completed Prelaunch Mode Determination Logic
    Switching from PRELAUNCH to LAUNCH
2021-01-14 Create nand.h
    Created and filled out the NAND header file
2021-01-14 Commonized sendSPI and recieveSPI to allow for both SPI busses to be used
2021-01-15 Updated reading monitoring data from gpio pins
2021-01-16 Moved macro location
2021-01-16 Made acquisition stable
2021-01-16 Updated Battery Voltage
2021-01-17 Additions to processing
2021-01-18 Updated imu struct and processing to better reflect aquired data
    Renamed struct members to reflect register names
    Changed types from floats to ints
    Added constants to divide with within processing
2021-01-18 Fixed local path
2021-01-18 Fixed Prelaunch transition algorithm
2021-01-18 Updated project clock settings
2021-01-19 Made build stable, Implemented retryTakeDelay with default constant defined in common.h
2021-01-19 Renamed interface files for more consistency
2021-01-19 Changed name in includes to reflect new name
2021-01-19 Moved NDEBUG definition to main.h, so it no longer had to be commented/uncommented
2021-01-19 Implemented Task timing
2021-01-20 Implemented loop_A()
2021-01-20 Fixed cast warnings when using testbed
2021-01-20 Implemented Circular Buffer into common files
2021-01-20 Updated determineStillness for circular buffer
2021-01-20 Updated common files to match dev branch
2021-01-21 Prepped for gpsRead() Implementation
2021-01-21 Fixed IncInterface Inclusion error
2021-01-21 Note on accel Z
2021-01-22 Added NAND interface code
2021-01-24 Programmed write functions
2021-01-24 Began setup of Nucleo test project
2021-01-26 initial gps read, not tested, cannot be called if time stamps are not matching
2021-01-26 Fixed infinite loop induced by testbed
2021-01-26 Waits for unlock before relocking
2021-01-26 Updated comment
2021-01-26 fixed infinite loop induced by testbed in other spot
2021-01-26 fix nmea erasing logic
2021-01-27 Setup Nucleo Test Project
2021-01-27 Fixed errors
2021-01-28 Overhauled print marcros
2021-01-28 Removed print artifacts
2021-01-28 Included retarget to main project
2021-01-28 Testing Nucleo project
2021-01-28 Corrected Nucleo project location
2021-01-28 coppied over full gpsNmea data to struct
2021-01-30 Renamed nucleo folders
2021-01-30 Created Monitoring Nucleo project
2021-01-30 Made Monitoring great again (GPIO tests)
2021-01-30 Made automatic links
2021-01-30 Moved PSP_GPIO functions to genericInterface from common
2021-01-30 Continued hardware interface design
2021-01-30 Added in storage function prototypes and began preparations for testbed
2021-01-30 Testbed preparations
2021-01-31 Changed data types from floats to int16_t for imu nodes
2021-01-31 Completed first iteration of Launch Transition
2021-01-31 Added VLQ logic
2021-02-01 Weeded out hardware inclusion errors
2021-02-01 Added spi inclusion to generic interface
2021-02-02 stopped gps read from running when recieving an identical packet
2021-02-02 Tested gps parsing
2021-02-03 Created Bank and LED constructors
2021-02-04 Implemented foundations of io banking
2021-02-04 Added Central LEDs to main.c
2021-02-04 minor fixes
2021-02-04 Added Nucleo Project
2021-02-04 Stabalized Testbed
2021-02-05 Create LICENSE
2021-02-05 Added Nucleo storage debugging. Made some fixes to nand code.
2021-02-05 This might work but I'm also exhausted
2021-02-05 Initialized spiLock as unlocked
2021-02-05 Fixed unlock bypass logic
2021-02-05 Removed obsolete print documentation from the main README
2021-02-06 debugging storage
2021-02-06 SPI Lock Debugging
2021-02-06 Added block erase function
2021-02-06 I think I fixed the spiLock implementation
2021-02-06 Updated storage setup function
2021-02-06 Avionics Bay
2021-02-06 broken dreams
2021-02-07 ADC WORKS
2021-02-07 Added PCB Files
2021-02-07 Beginning of the writing to file/storage function
2021-02-07 storage debugging
2021-02-07 Started MITCH_2021-48 project
2021-02-07 Setup 48 pin project
2021-02-08 Started 48 pin project
2021-02-08 Added Shift Registeres, Split Octal Buffers
2021-02-09 storage debug
2021-02-09 Replaces shift registers with dual quad
2021-02-09 further storage debugging
2021-02-10 Completed VLQ functions
2021-02-11 Nucleo Sensor Stable Build Before adding gps driver
2021-02-11 Update to PCB
2021-02-11 further nand debugging
2021-02-11 Combined sensor block with processor block
2021-02-12 Documented debug storage testbed and fixed/added some more code
2021-02-14 Write to File function fixed and added in defined function returns
2021-02-14 Updated function name
2021-02-14 DaqStatus Compression
2021-02-14 Added Struct Data Bytes
2021-02-14 Worked on Data Compression for GPS and Processed Data. Added variables to common.h for the processedData Struct
2021-02-14 Added More Struct compression functions
2021-02-17 Debugging of Storage
2021-02-17 Updated compression of IMU Data
2021-02-17 Updated common.c
2021-02-17 Restored nandInterface to working state
2021-02-17 Moved Hardware Design to different Github
2021-02-17 Updated Location of WriteToStorage Function
2021-02-17 Fixed ADC issues in storage
2021-02-21 Adding Code (NOT FINAL)
2021-02-25 IMU interfaces written
    Still need to test, but this should be the code to get accel, gyro, and mag data.
2021-03-06 Stable Control Logic
2021-03-08 Updated common.h to match controlLogic branch
